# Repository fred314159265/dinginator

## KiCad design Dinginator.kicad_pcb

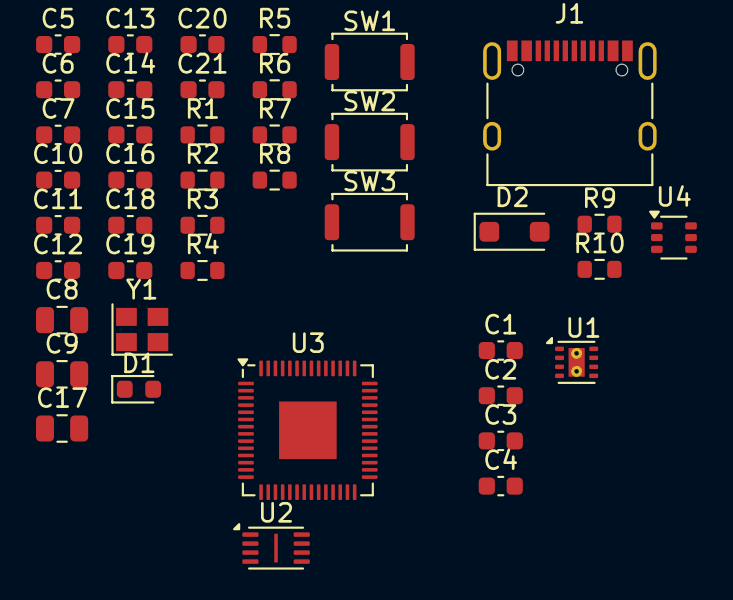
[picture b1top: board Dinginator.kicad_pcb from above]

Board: 2 copper layers, 42 parts (0 on the bottom side), 28 nets, no tracks yet.

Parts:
C1, C4: 10uF; C_0603_1608Metric
C2, C3: 100nF; C_0603_1608Metric
C5, C7: 30p; C_0603_1608Metric
C6, C10, C11, C12, C13, C14, C15, C16, C18, C19, C20, C21: 100n; C_0603_1608Metric
C8, C9, C17: 2.2u; C_0805_2012Metric
D1: 3V3; LED_0603_1608Metric
D2: 40V 1A; D_SOD-123F
J1: USB_C_Receptacle_USB2.0; USB_C_Receptacle_XKB_U262-16XN-4BVC11
R1, R3, R7: 10k; R_0603_1608Metric
R2, R4: 1k; R_0603_1608Metric
R5, R6: 27R; R_0603_1608Metric
R8: 255R; R_0603_1608Metric
R9, R10: 5.1k; R_0603_1608Metric
SW1: RST; SW_Push_SPST_NO_Alps_SKRK
SW2: USB_BOOT; SW_Push_SPST_NO_Alps_SKRK
SW3: USER_SW; SW_Push_SPST_NO_Alps_SKRK
U1: DRV8837; WSON-8-1EP_2x2mm_P0.5mm_EP0.9x1.6mm_ThermalVias
U2: W25Q80DVUXIE; Winbond_USON-8-1EP_3x2mm_P0.5mm_EP0.2x1.6mm
U3: RP2040; QFN-56-1EP_7x7mm_P0.4mm_EP3.2x3.2mm
U4: TPD4E1U06DCKR; SOT-363_SC-70-6
Y1: 12MHz; Crystal_SMD_2520-4Pin_2.5x2.0mm

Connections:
+3V3: R1.2, SW3.2
/CC1: J1.A5 (CC1), R9.1
/CC2: J1.B5 (CC2), R10.1
/RP2040/1V1: C13.1, C15.1, C17.1, U3.23 (DVDD), U3.45 (VREG_VOUT), U3.50 (DVDD)
/RP2040/3V3_IN: C8.1, C9.1, C10.1, C11.1, C12.1, C14.1, C16.1, C18.1, C19.1, C20.1, R3.2, U2.8 (VCC), U3.1 (IOVDD), U3.10 (IOVDD), U3.22 (IOVDD), U3.33 (IOVDD), U3.42 (IOVDD), U3.43 (ADC_AVDD), U3.44 (VREG_VIN), U3.48 (USB_VDD), U3.49 (IOVDD)
/RP2040/QSPI_SCLK: U2.6 (CLK), U3.52 (QSPI_SCLK)
/RP2040/QSPI_SD0: U2.5 (DI(IO0)), U3.53 (QSPI_SD0)
/RP2040/QSPI_SD1: U2.2 (DO(IO1)), U3.55 (QSPI_SD1)
/RP2040/QSPI_SD2: U2.3 (~WP(IO2)), U3.54 (QSPI_SD2)
/RP2040/QSPI_SD3: U2.7 (~HOLD(IO3)), U3.51 (QSPI_SD3)
/RP2040/QSPI_SS: R3.1, R4.2, U2.1 (~CS), U3.56 (QSPI_CSN)
/RP2040/USB_PT_D+: R6.1, U3.47 (USB_DP)
/RP2040/USB_PT_D-: R5.1, U3.46 (USB_DM)
/RP2040/USER_BUTT: C21.1, R7.2, SW3.1, U3.12 (GPIO9)
/RP2040/USER_LED: R8.1, U3.13 (GPIO10)
/RP2040/XIN: C5.2, U3.20 (XIN), Y1.1
/RP2040/XOUT: R2.1, U3.21 (XOUT)
/RP2040/~RESET: C6.1, R1.1, SW1.2, U3.26 (RUN)
/Solenoid Driver/0V: C1.2, C2.2, C3.2, C4.2, U1.4 (GND), U1.9 (GND)
/Solenoid Driver/V_LOGIC: C2.1, U1.8 (VCC)
/Solenoid Driver/V_MOTOR: C1.1, C3.1, C4.1, U1.1 (VM)
/USB_D+: J1.A6 (D+), J1.B6 (D+), U4.3 (D2+)
/USB_D-: J1.A7 (D-), J1.B7 (D-), U4.4 (D2-)
/USB_VBUS: D2.2 (A), J1.A4 (VBUS), J1.A9 (VBUS), J1.B4 (VBUS), J1.B9 (VBUS)
GND: C5.1, C6.2, C7.2, C8.2, C9.2, C10.2, C11.2, C12.2, C13.2, C14.2, C15.2, C16.2, C17.2, C18.2, C19.2, C20.2, C21.2, D1.1 (K), J1.A1 (GND), J1.A12 (GND), J1.B1 (GND), J1.B12 (GND), J1.S1 (SHIELD), R7.1, R9.2, R10.2, SW1.1, SW2.2, U3.19 (TESTEN), U3.57 (GND), U4.2 (G), Y1.2, Y1.4
unnamed: C7.1, R2.2, Y1.3
unnamed: D1.2 (A), R8.2
unnamed: R4.1, SW2.1

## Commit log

2024-09-25 Started working on it.
2025-03-05 Progress?
